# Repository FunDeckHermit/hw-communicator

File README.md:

# HW-communicator
Devices that can communicate state to one another. 

Project uses a Raspberry Pi Pico W, a Lora antenna, TP4056 lithium-ion cell charger to transmit a selected phrase.
This selected phrase is picked up by another module and displayed.

All firmware code is written in micropython. 

Todo: 
 * Wifi communication
 * LoraWAN communication
 * Pickup firmware
 
What would I do differently:
 * Add USB-B port somewhere
 * Add buzzer
 * Move 18650 holder a bit higher

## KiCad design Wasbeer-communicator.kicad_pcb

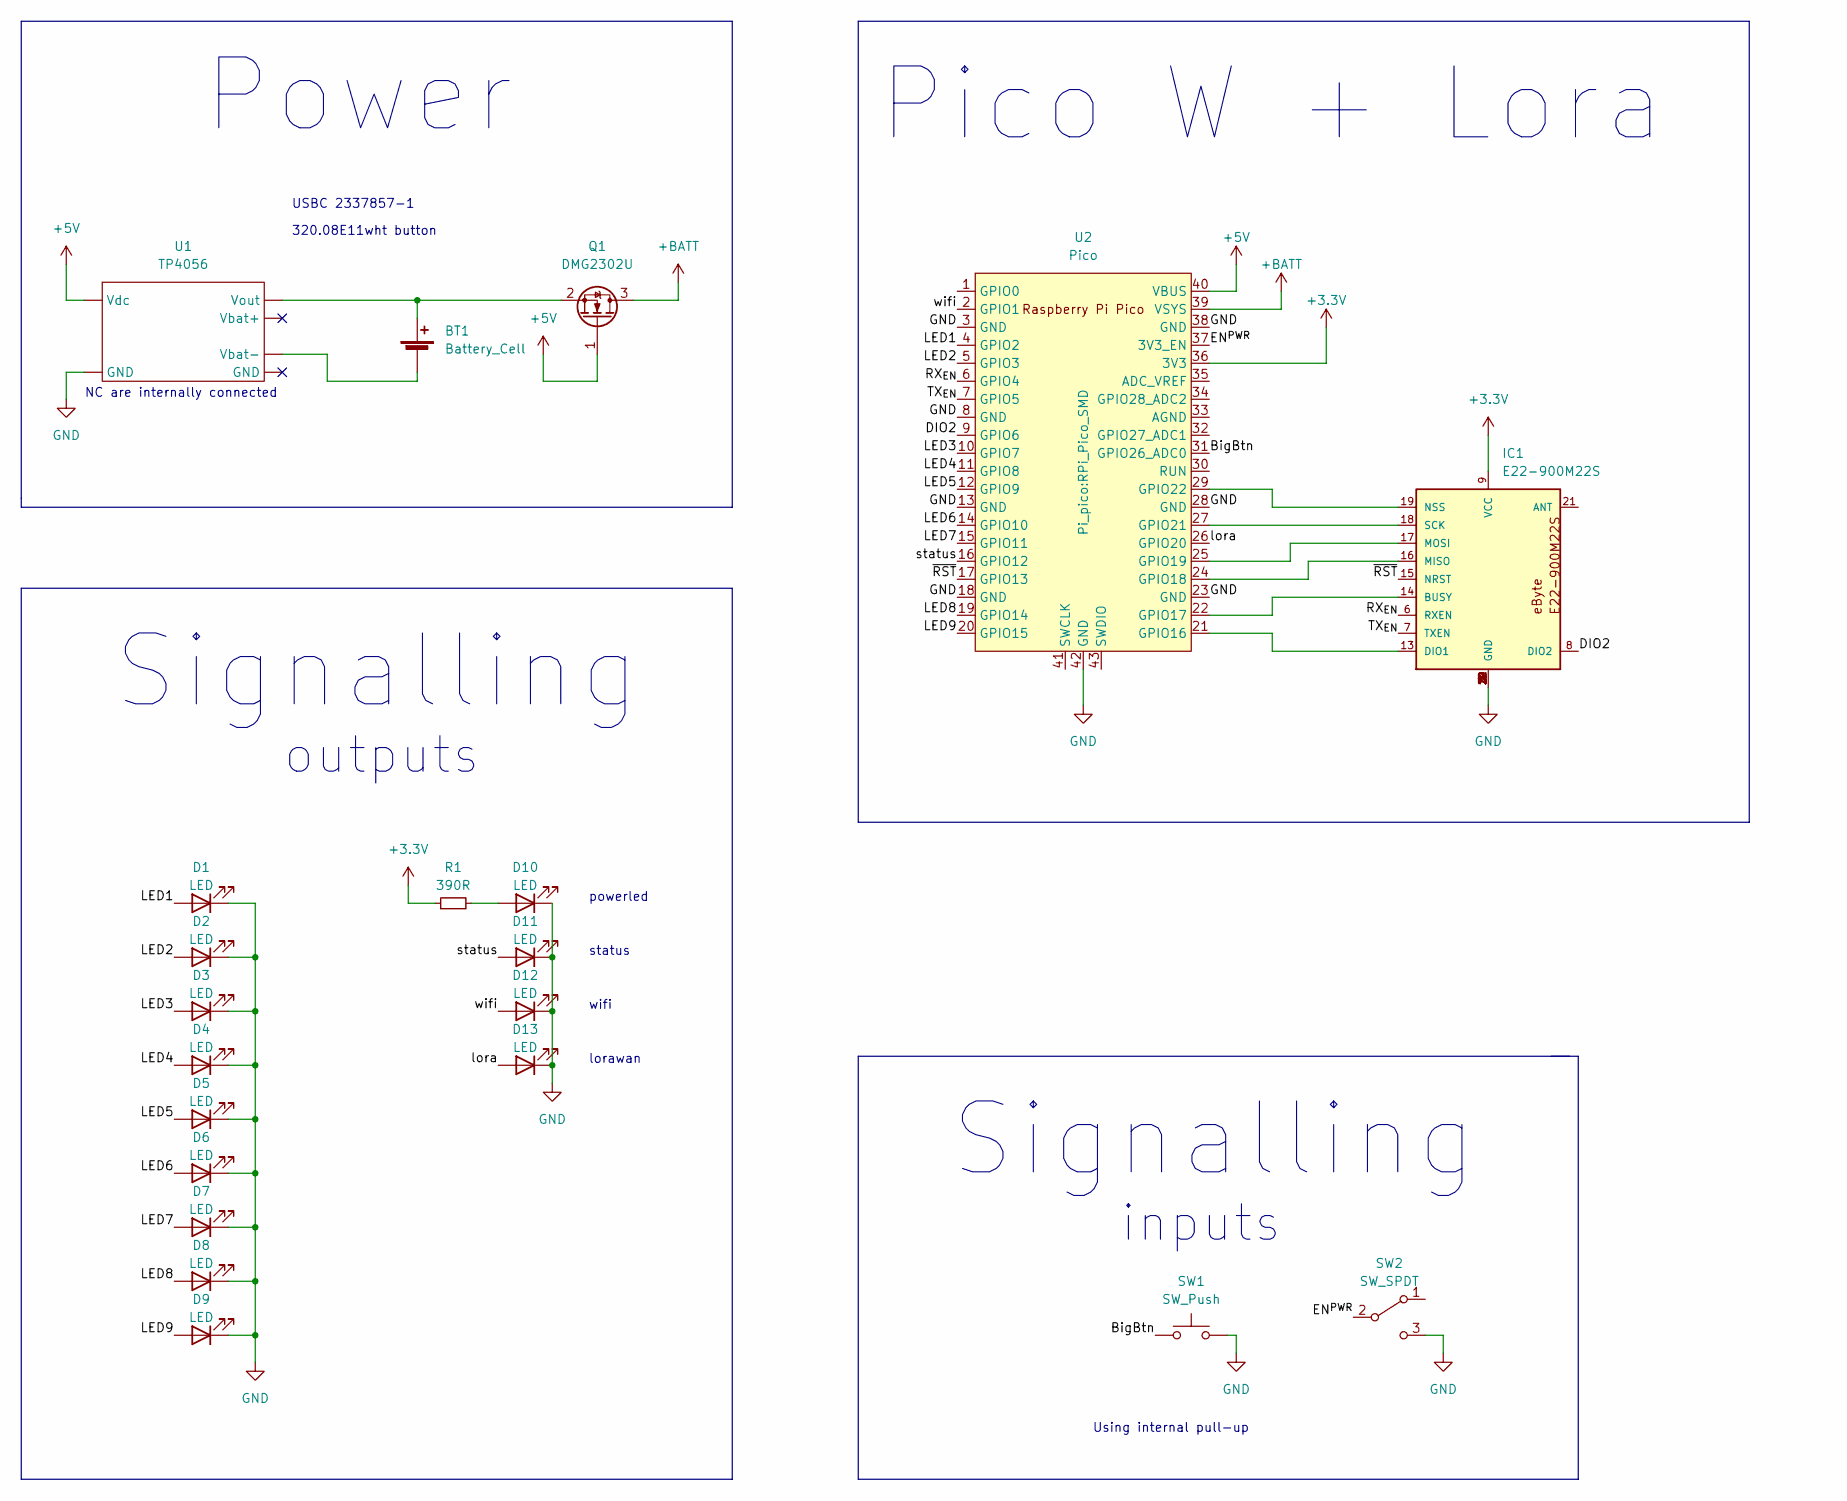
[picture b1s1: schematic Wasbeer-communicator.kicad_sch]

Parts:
BT1: Battery_Cell; 1042P
D1, D2, D3, D4, D5, D6, D7, D8, D9: LED; WL-SMDC
D10, D11, D12, D13: LED; LED_0603_1608Metric_Pad1.05x0.95mm_HandSolder
IC1: E22-900M22S
Q1: DMG2302U; SOT-23
R1: 390R; R_1206_3216Metric
SW1: SW_Push; 320.08E11wht
SW2: SW_SPDT; MSS3-Q-TR
U1: TP4056; TP4056-Module
U2: Pico; RPi_Pico_SMD

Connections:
+3.3V: IC1.9 (VCC), R1.1, U2.36 (3V3)
+5V: Q1.1 (G), U1.1 (Vdc), U2.40 (VBUS)
+BATT: Q1.3 (D), U2.39 (VSYS)
/BigBtn: SW1.1, U2.31 (GPIO26_ADC0)
/DIO2: IC1.8 (DIO2), U2.9 (GPIO6)
/EN^{PWR}: SW2.2 (B), U2.37 (3V3_EN)
/LED1: D1.2 (A), U2.4 (GPIO2)
/LED2: D2.2 (A), U2.5 (GPIO3)
/LED3: D3.2 (A), U2.10 (GPIO7)
/LED4: D4.2 (A), U2.11 (GPIO8)
/LED5: D5.2 (A), U2.12 (GPIO9)
/LED6: D6.2 (A), U2.14 (GPIO10)
/LED7: D7.2 (A), U2.15 (GPIO11)
/LED8: D8.2 (A), U2.19 (GPIO14)
/LED9: D9.2 (A), U2.20 (GPIO15)
/RX_{EN}: IC1.6 (RXEN), U2.6 (GPIO4)
/TX_{EN}: IC1.7 (TXEN), U2.7 (GPIO5)
/lora: D13.2 (A), U2.26 (GPIO20)
/status: D11.2 (A), U2.16 (GPIO12)
/wifi: D12.2 (A), U2.2 (GPIO1)
/~RST: IC1.15 (NRST), U2.17 (GPIO13)
GND: D1.1 (K), D2.1 (K), D3.1 (K), D4.1 (K), D5.1 (K), D6.1 (K), D7.1 (K), D8.1 (K), D9.1 (K), D10.1 (K), D11.1 (K), D12.1 (K), D13.1 (K), IC1.1 (GND), IC1.2 (GND), IC1.3 (GND), IC1.4 (GND), IC1.5 (GND), IC1.10 (GND), IC1.11 (GND), IC1.12 (GND), IC1.20 (GND), IC1.22 (GND), SW1.2, SW2.3 (C), U1.2 (GND), U2.3 (GND), U2.8 (GND), U2.13 (GND), U2.18 (GND), U2.23 (GND), U2.28 (GND), U2.38 (GND), U2.42 (GND)
unnamed: BT1.1 (+), Q1.2 (S), U1.3 (Vout)
unnamed: BT1.2 (-), U1.6 (Vbat-)
unnamed: D10.2 (A), R1.2
unnamed: IC1.13 (DIO1), U2.21 (GPIO16)
unnamed: IC1.14 (BUSY), U2.22 (GPIO17)
unnamed: IC1.16 (MISO), U2.24 (GPIO18)
unnamed: IC1.17 (MOSI), U2.25 (GPIO19)
unnamed: IC1.18 (SCK), U2.27 (GPIO21)
unnamed: IC1.19 (NSS), U2.29 (GPIO22)

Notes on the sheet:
USBC 2337857-1
Signalling
Pico W + Lora
NC are internally connected
Power
Using internal pull-up
lorawan
outputs
status
powerled
wifi
inputs
320.08E11wht button

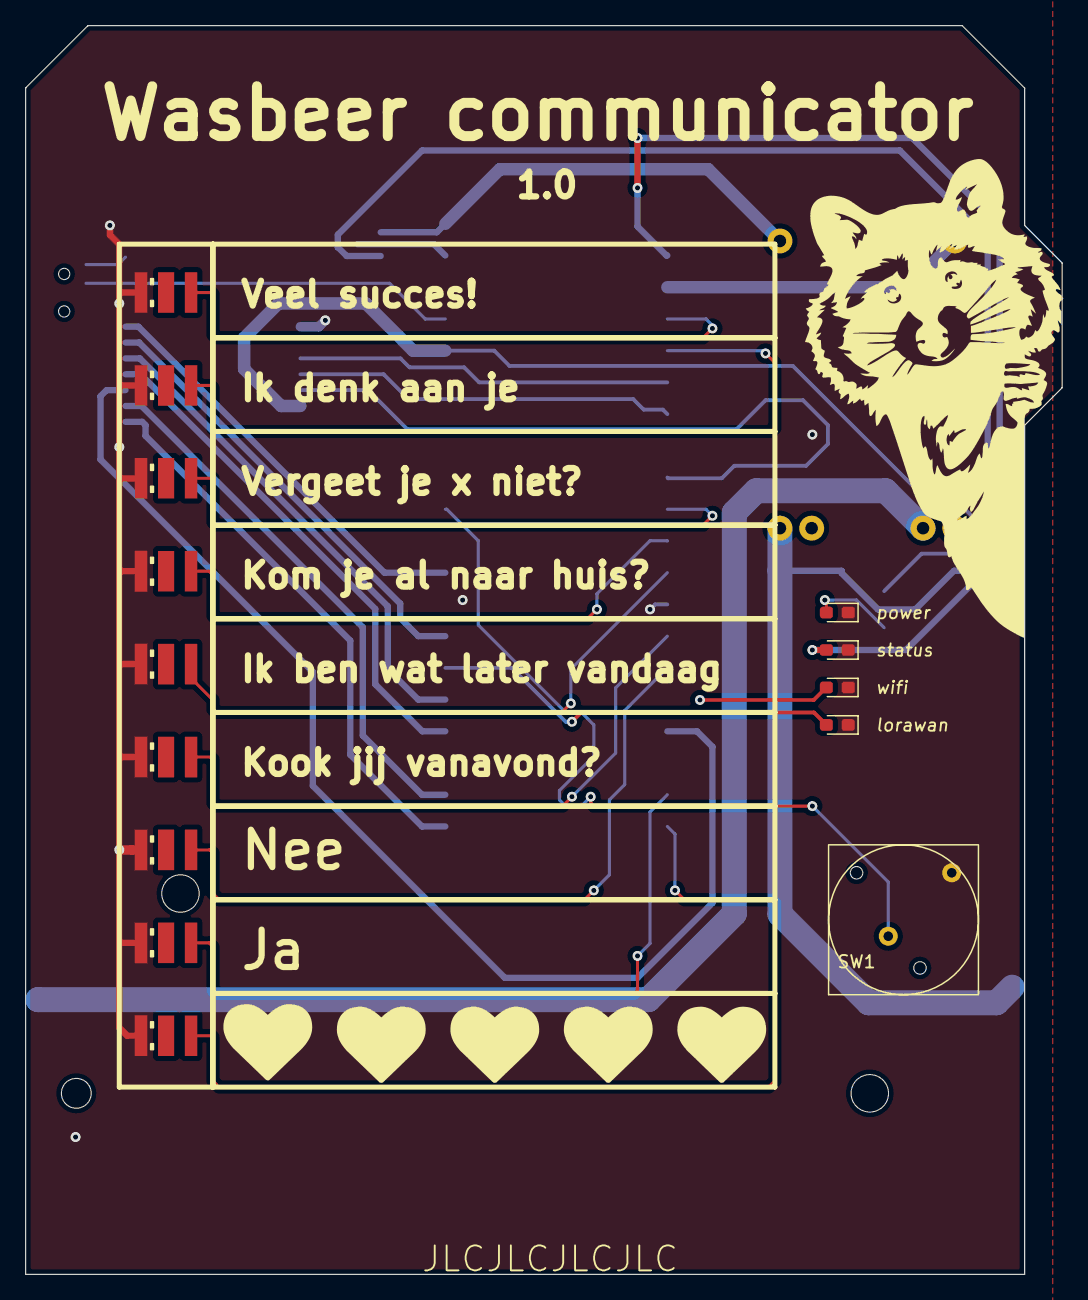
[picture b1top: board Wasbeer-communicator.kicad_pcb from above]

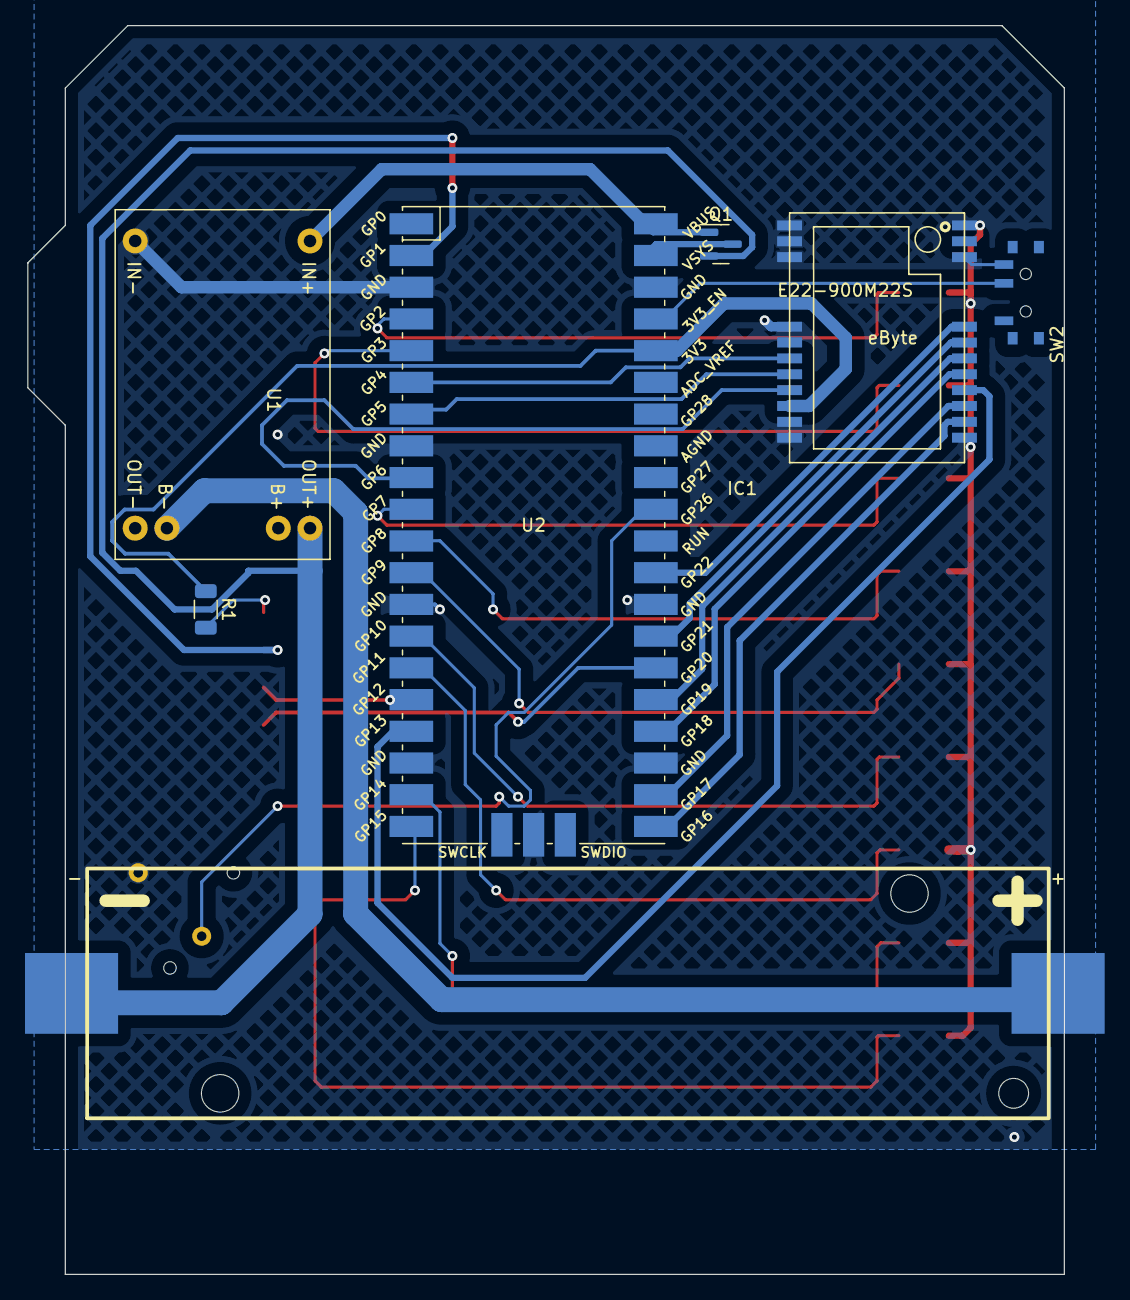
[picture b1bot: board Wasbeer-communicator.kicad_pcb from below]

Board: 2 copper layers, 83.0 x 100.0 mm, 21 parts (7 on the bottom side), 31 nets.

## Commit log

2022-11-02 Added battery holder
2022-11-02 Added eByte E22-900M22S module to schematic
2022-11-02 Added text
2022-11-02 another 3 hours of work
2022-11-03 Finished design, created gerbers for lcsc
2022-11-13 Added firmware
2022-11-13 Removed some files
2022-11-19 Firmware: PWM the leds and enhanced state machine
2022-11-20 Firmware: Started on Wifi with phew! library
2022-11-27 Micropython has a nasty bug, so changed to Arduino
2022-11-27 Removed some backup files
